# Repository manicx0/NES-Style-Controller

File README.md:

### NES-Style Modern Controller — Component List & Wiring Overview

An SoC with built-in WiFi+Bluetooth handles wireless duty, with an optional dedicated 2.4GHz nRF radio for a low-latency "wired-like" mode — a common approach in hobby gamepad builds since no single chip natively does WiFi+BT+proprietary-nRF all at once.

### Component List

**Brain**

- Main MCU/SoC with built-in WiFi + Bluetooth (e.g. an ESP32-class chip) — handles button/stick polling, display driving, and wireless output
- Optional secondary 2.4GHz radio module (nRF24L01+ style) for a dedicated low-latency "nRF mode," wired to the MCU over SPI

**Input**

- 2x analog stick modules (dual-potentiometer + click-button type, PSP/Joy-Con style)
- D-pad (4-way cross, either 4 discrete tactile switches or a single 4/8-way rocker module)
- 4x face buttons (tactile switches)
- Start/Select buttons
- 1-2x dedicated "menu/mode" buttons for navigating the mini display's settings UI (can double up with Start/Select if you want to save parts)
- Tactile switch caps / keycaps for the above

**Display**

- Small SPI or I2C TFT/OLED display (roughly 0.9"–1.5" is typical for a corner status screen)

**Power**

- LiPo battery (single-cell, capacity to taste)
- Battery charge/protection module (handles USB-C charging + over-discharge protection)
- 3.3V voltage regulator (if your battery/charger output doesn't already give clean 3.3V)
- USB-C connector (charging + optional wired/data mode)
- Power slide switch

**Support**

- Pull-down (or pull-up) resistors for each button line, unless using MCU internal pull resistors
- Small decoupling capacitors near MCU and radio modules
- Status LED(s) (battery/pairing indicator — optional)
- Protoboard or custom PCB
- 3D-printed or laser-cut rectangular shell (NES-004 proportions, no shoulder-button cutouts)

## Acknowledgments / Inspiration

Design inspired by the NES 004 controller form factor.

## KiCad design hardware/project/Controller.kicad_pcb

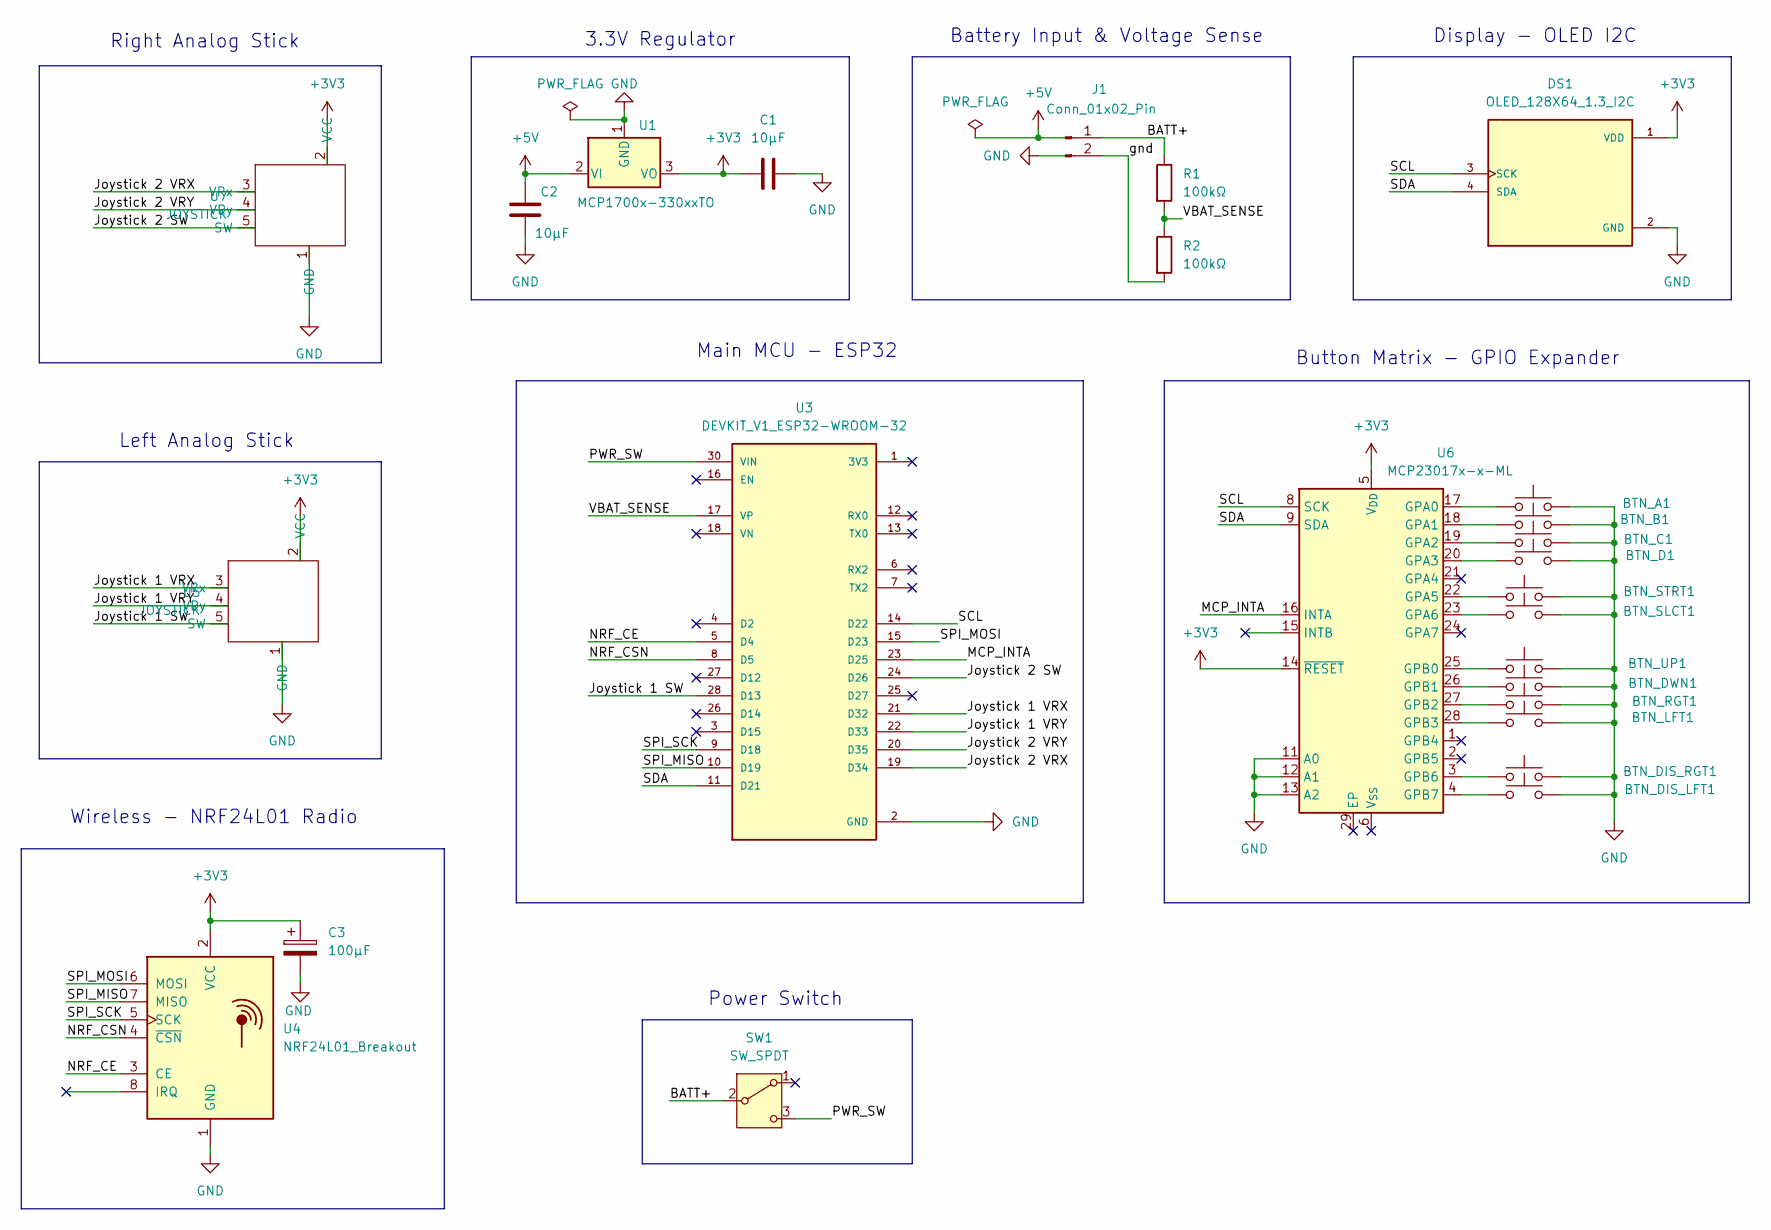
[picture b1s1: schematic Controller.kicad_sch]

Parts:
BTN_A1: SW_Push; SW_PUSH-12mm
BTN_B1: SW_Push; SW_PUSH-12mm
BTN_C1: SW_Push; SW_PUSH-12mm
BTN_D1: SW_Push; SW_PUSH-12mm
BTN_DIS_LFT1: SW_Push; SW_SPST_PTS647_Sx50
BTN_DIS_RGT1: SW_Push; SW_SPST_PTS647_Sx50
BTN_DWN1: SW_Push; SW_PUSH-12mm
BTN_LFT1: SW_Push; SW_PUSH-12mm
BTN_RGT1: SW_Push; SW_PUSH-12mm
BTN_SLCT1: SW_Push; SW_SPST_PTS647_Sx50
BTN_STRT1: SW_Push; SW_SPST_PTS647_Sx50
BTN_UP1: SW_Push; SW_PUSH-12mm
C1, C2: 10µF; C_0805_2012Metric_Pad1.18x1.45mm_HandSolder
C3: 100µF; CP_Radial_D8.0mm_P3.50mm
DS1: OLED_128X64_1.3_I2C; LCD_OLED_128X64_1.3_I2C; PARTREV NA
J1: Conn_01x02_Pin; JST_XA_B02B-XASK-1_1x02_P2.50mm_Vertical
R1, R2: 100kΩ; R_0805_2012Metric_Pad1.20x1.40mm_HandSolder
SW1: SW_SPDT; SW_SPDT_PCM12
U1: MCP1700x-330xxTO; TO-92_Inline
U3: DEVKIT_V1_ESP32-WROOM-32; MODULE_DEVKIT_V1_ESP32-WROOM-32
U4: NRF24L01_Breakout; nRF24L01_Breakout
U5, U7: JOYSTICK
U6: MCP23017x-x-ML; QFN-28-1EP_6x6mm_P0.65mm_EP4.25x4.25mm

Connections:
+3V3: C1.1, C3.1, DS1.1 (VDD), U1.3 (VO), U4.2 (VCC), U5.2 (VCC), U6.5 (V_{DD}), U6.14 (~RESET), U7.2 (VCC)
+5V: C2.1, U1.2 (VI)
/BATT+: J1.1, R1.1, SW1.2 (B)
/Joystick 1 SW: U3.28 (D13), U5.5 (SW)
/Joystick 1 VRX: U3.21 (D32), U5.3 (VRx)
/Joystick 1 VRY: U3.22 (D33), U5.4 (VRy)
/Joystick 2 SW: U3.24 (D26), U7.5 (SW)
/Joystick 2 VRX: U3.19 (D34), U7.3 (VRx)
/Joystick 2 VRY: U3.20 (D35), U7.4 (VRy)
/MCP_INTA: U3.23 (D25), U6.16 (INTA)
/NRF_CE: U3.5 (D4), U4.3 (CE)
/NRF_CSN: U3.8 (D5), U4.4 (~CSN)
/PWR_SW: SW1.3 (C), U3.30 (VIN)
/SCL: DS1.3 (SCK), U3.14 (D22), U6.8 (SCK)
/SDA: DS1.4 (SDA), U3.11 (D21), U6.9 (SDA)
/SPI_MISO: U3.10 (D19), U4.7 (MISO)
/SPI_MOSI: U3.15 (D23), U4.6 (MOSI)
/SPI_SCK: U3.9 (D18), U4.5 (SCK)
/VBAT_SENSE: R1.2, R2.1, U3.17 (VP)
/gnd: J1.2, R2.2
GND: BTN_A1.2, BTN_B1.2, BTN_C1.2, BTN_D1.2, BTN_DIS_LFT1.2, BTN_DIS_RGT1.2, BTN_DWN1.2, BTN_LFT1.2, BTN_RGT1.2, BTN_SLCT1.2, BTN_STRT1.2, BTN_UP1.2, C1.2, C2.2, C3.2, DS1.2 (GND), U1.1 (GND), U3.2 (GND), U3.29 (GND), U4.1 (GND), U5.1 (GND), U6.11 (A0), U6.12 (A1), U6.13 (A2), U7.1 (GND)
unnamed: BTN_A1.1, U6.17 (GPA0)
unnamed: BTN_B1.1, U6.18 (GPA1)
unnamed: BTN_C1.1, U6.19 (GPA2)
unnamed: BTN_D1.1, U6.20 (GPA3)
unnamed: BTN_STRT1.1, U6.22 (GPA5)
unnamed: BTN_SLCT1.1, U6.23 (GPA6)
unnamed: BTN_UP1.1, U6.25 (GPB0)
unnamed: BTN_DWN1.1, U6.26 (GPB1)
unnamed: BTN_RGT1.1, U6.27 (GPB2)
unnamed: BTN_LFT1.1, U6.28 (GPB3)
unnamed: BTN_DIS_RGT1.1, U6.3 (GPB6)
unnamed: BTN_DIS_LFT1.1, U6.4 (GPB7)

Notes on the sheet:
Wireless - NRF24L01 Radio
Right Analog Stick
Main MCU - ESP32
Button Matrix - GPIO Expander
3.3V Regulator
Left Analog Stick
Power Switch
Battery Input & Voltage Sense
Display - OLED I2C

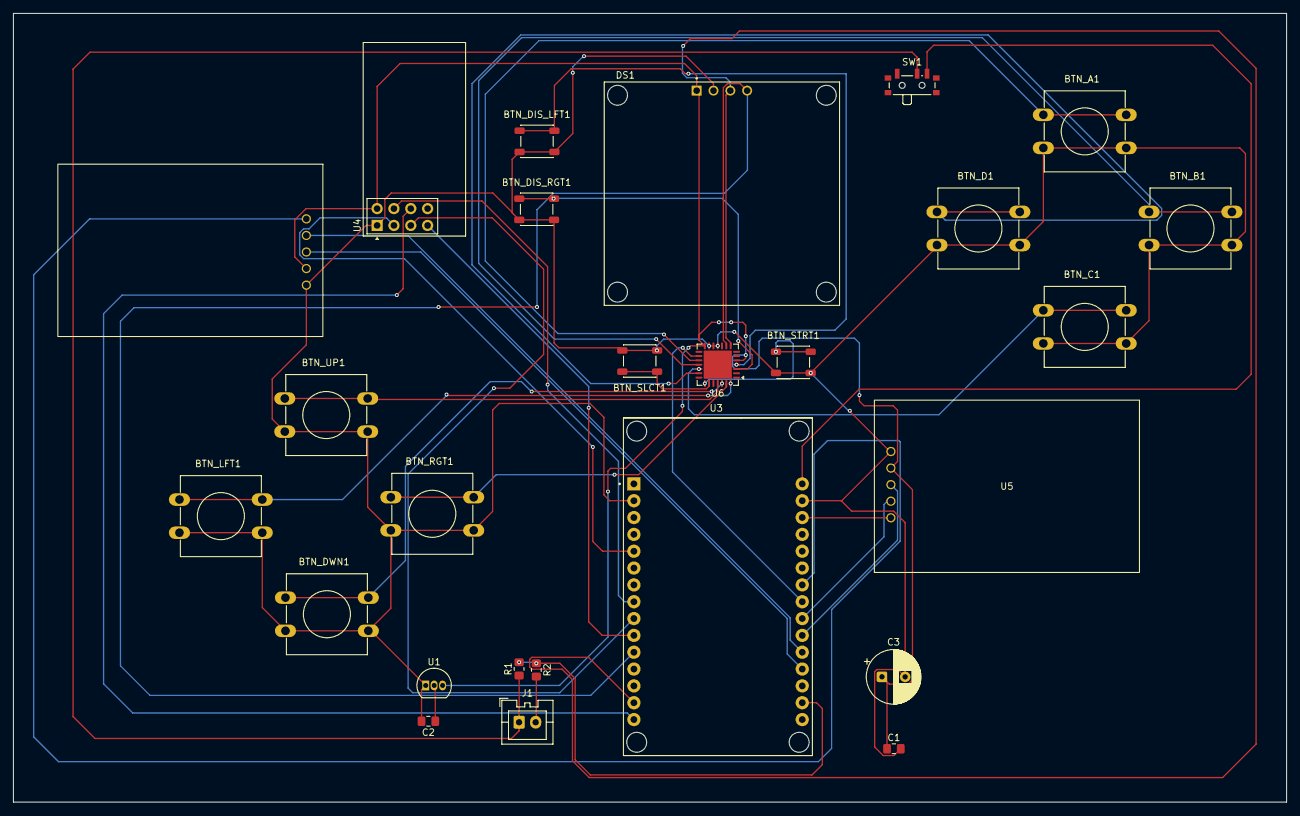
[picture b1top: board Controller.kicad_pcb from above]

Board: 2 copper layers, 192.1 x 119.0 mm, 26 parts (0 on the bottom side), 33 nets.
